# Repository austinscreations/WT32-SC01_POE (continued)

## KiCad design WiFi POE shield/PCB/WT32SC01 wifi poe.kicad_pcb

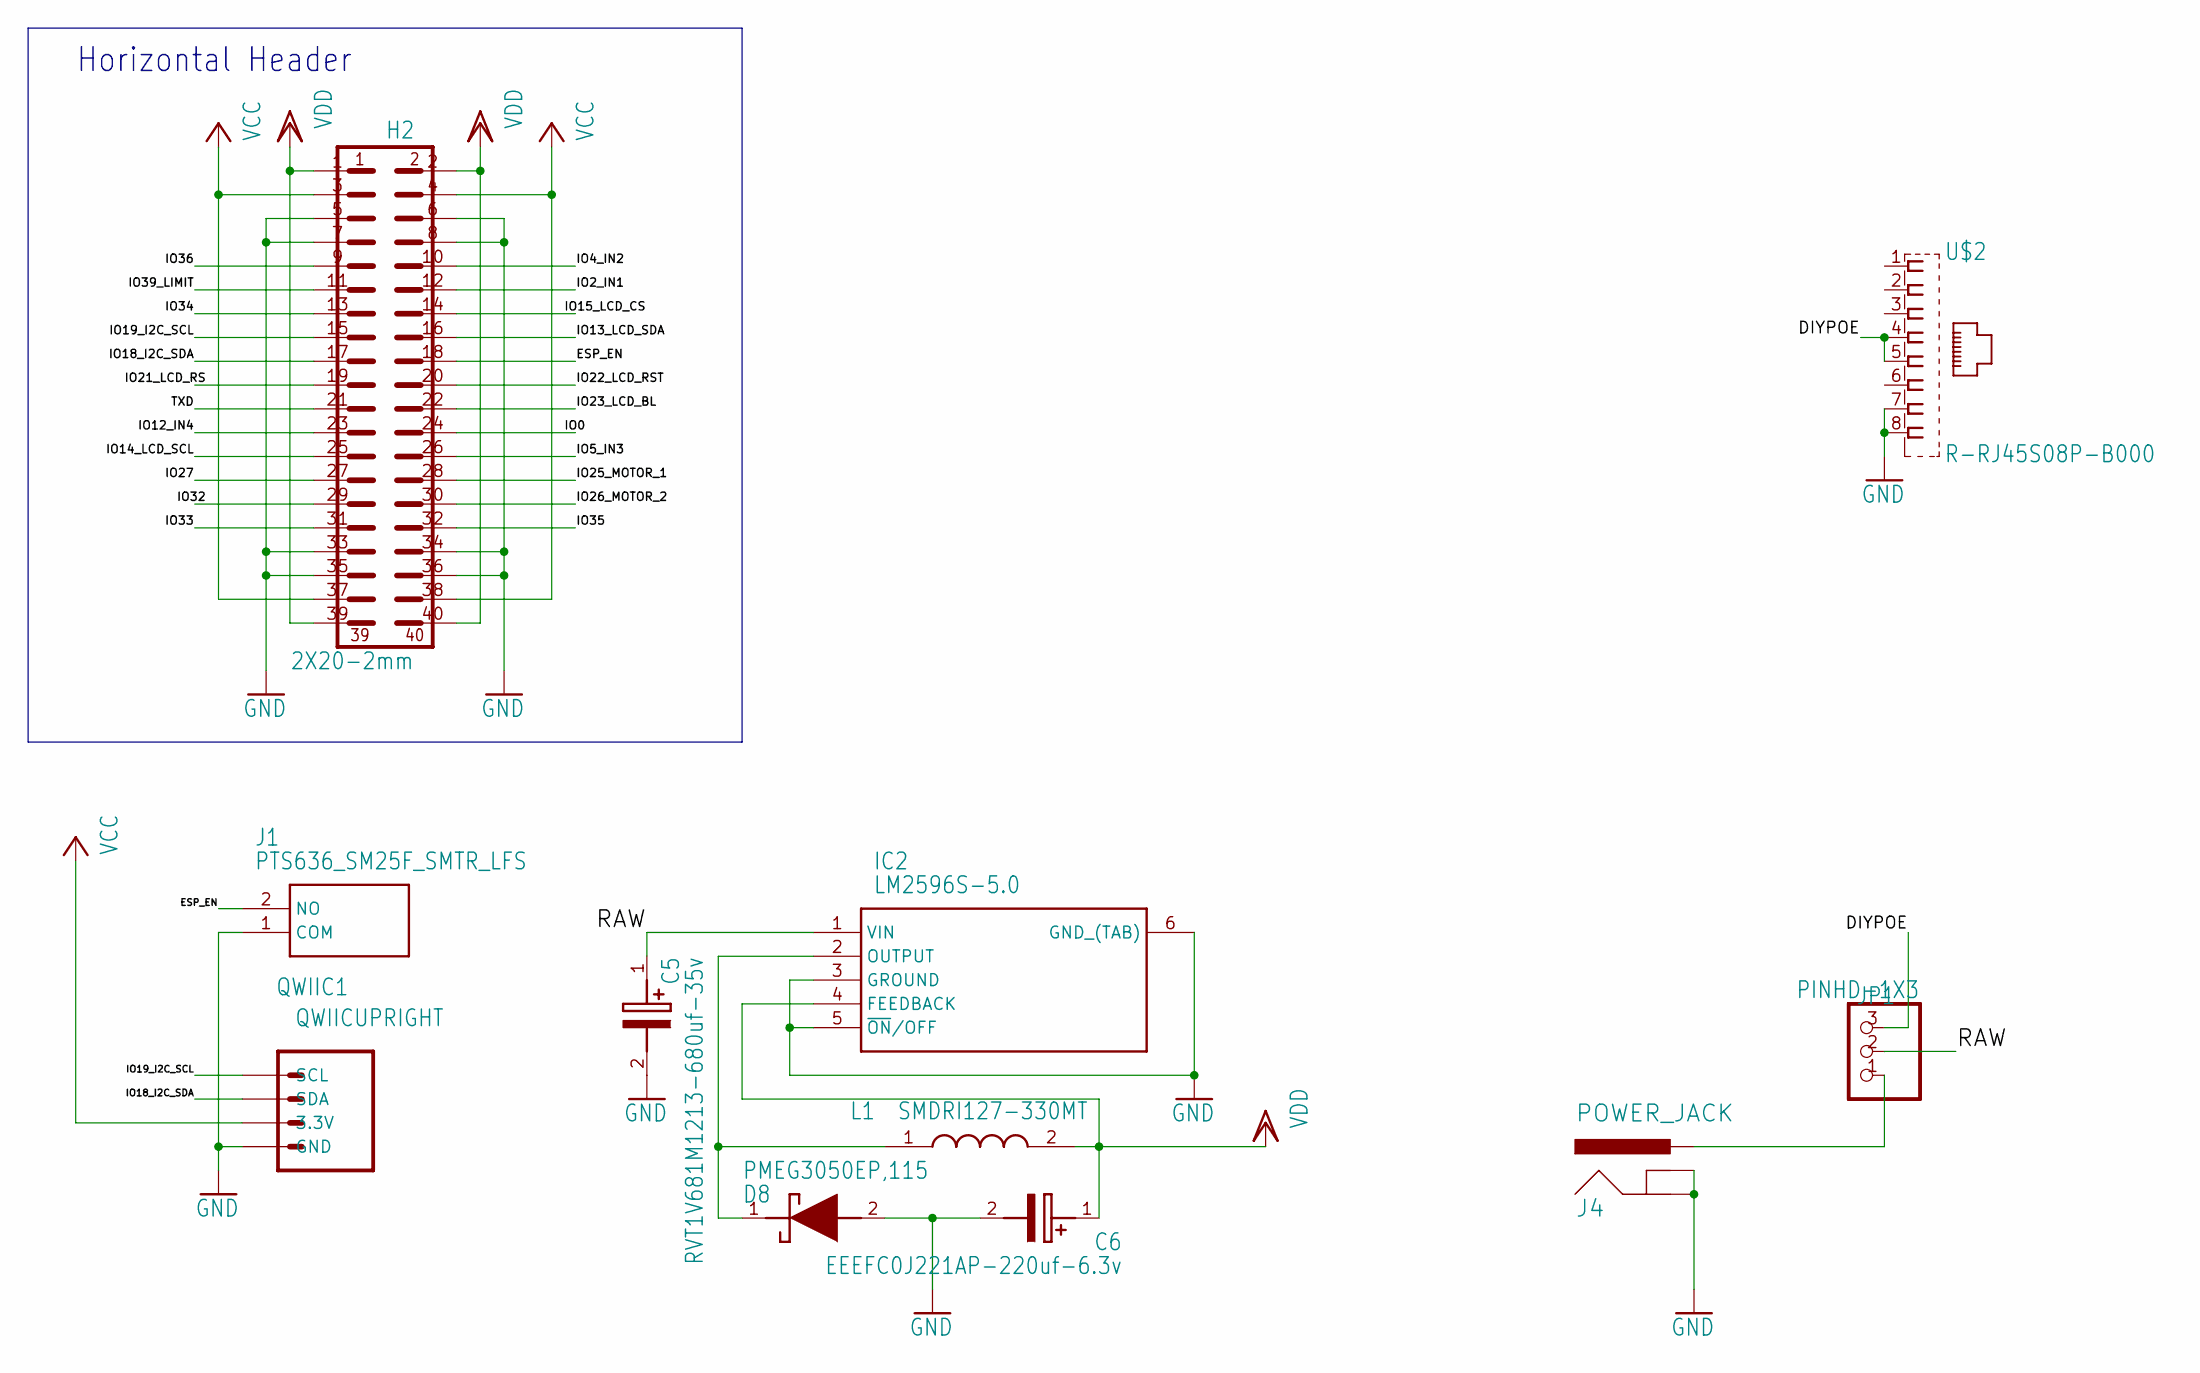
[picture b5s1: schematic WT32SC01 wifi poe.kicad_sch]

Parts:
C5: RVT1V681M1213-680uf-35v; CAPAE1350X1400N
C6: EEEFC0J221AP-220uf-6.3v; CAPAE830X650N
D8: PMEG3050EP,115; PMEG3050EP115
H2: 2X20-2mm; 2X20-2.00-P-BELOW
IC2: LM2596S-5.0; TO170P1435X465-6N
J1: PTS636_SM25F_SMTR_LFS; PTS636SM25FSMTRLFS
J4: POWER_JACK; POWER_JACK_PTH
JP1: PINHD-1X3; 1X03
L1: SMDRI127-330MT; INDPM120120X800N
QWIIC1: QWIICUPRIGHT; BM04B-SRSS-TB
U$2: R-RJ45S08P-B000

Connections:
DIYPOE: JP1.3, U$2.4, U$2.5
ESP_EN: H2.18, J1.2 (NO)
GND: C5.2 (-), C6.2 (-), D8.2 (A), H2.5, H2.6, H2.7, H2.8, H2.33, H2.34, H2.35, H2.36, IC2.3 (GROUND), IC2.5 (~ON/OFF), IC2.6 (GND_(TAB)), J1.1 (COM), J4.GND, J4.GNDBREAK, QWIIC1.1 (GND), U$2.7, U$2.8
IO0: H2.24
IO2_IN1: H2.12
IO4_IN2: H2.10
IO5_IN3: H2.26
IO12_IN4: H2.23
IO13_LCD_SDA: H2.16
IO14_LCD_SCL: H2.25
IO15_LCD_CS: H2.14
IO18_I2C_SDA: H2.17, QWIIC1.3 (SDA)
IO19_I2C_SCL: H2.15, QWIIC1.4 (SCL)
IO21_LCD_RS: H2.19
IO22_LCD_RST: H2.20
IO23_LCD_BL: H2.22
IO25_MOTOR_1: H2.28
IO26_MOTOR_2: H2.30
IO27: H2.27
IO32: H2.29
IO33: H2.31
IO34: H2.13
IO35: H2.32
IO36: H2.9
IO39_LIMIT: H2.11
unnamed: J4.PWR, JP1.1
unnamed: D8.1 (K), IC2.2 (OUTPUT), L1.1
RAW: C5.1 (+), IC2.1 (VIN), JP1.2
TXD: H2.21
VCC: H2.3, H2.4, H2.37, H2.38, QWIIC1.2 (3.3V)
VDD: C6.1 (+), H2.1, H2.2, H2.39, H2.40, IC2.4 (FEEDBACK), L1.2

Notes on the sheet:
Horizontal Header

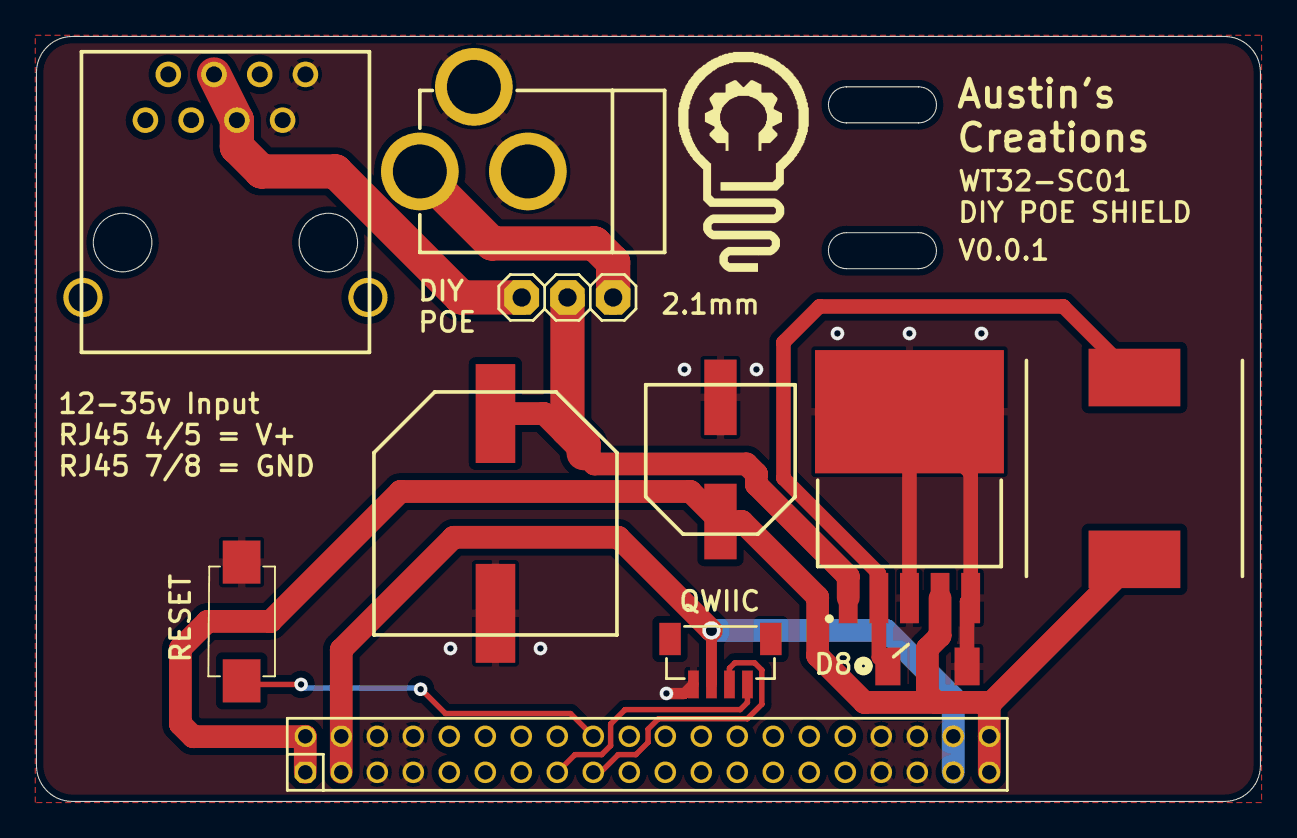
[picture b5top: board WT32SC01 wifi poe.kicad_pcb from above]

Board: 2 copper layers, 68.0 x 42.5 mm, 12 parts (0 on the bottom side), 10 nets.

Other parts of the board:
U$1: LOGOMED

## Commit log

2022-03-18 adding custom 3d printable wall plate mount
2022-03-18 example code
2022-03-26 accidental upload
2022-06-23 update for new boards
2022-06-23 preparing repo overhaul
2022-06-23 add new wifi and ethernet designs
2022-06-28 new versions
2022-06-28 obsolete design
2022-06-29 add case option for no usb
2022-06-29 add no usb case options
2023-06-28 adding latest POE shield
2023-08-02 adding 86s panel support
2023-08-02 add schematic image
2023-09-18 nudging the large inductor
2023-09-18 nudged the large inductor
2023-09-18 update inductor footprint
2024-05-23 rev 6 obsolete
    5v regulator not stable long term - new design coming
2024-05-23 add plus screen POE NA screen mount
2024-09-11 add the holder for the wt32sc01-plus screen
2024-09-11 Revert "add the holder for the wt32sc01-plus screen"
    This reverts commit c838f73afda2a925ba6b19c164f577740880c950.
